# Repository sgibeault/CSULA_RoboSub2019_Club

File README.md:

# CSULA_RoboSub2019_Club
Files for the CSULA RoboSub 2019 club submarine. Her name is M4G1K4RP. 

Sidra's tasks for this week (6/10/19):
- Test barometer in yellow tub in the lab (Tuesday)
- Solder battery connectors and see if we could use the longer tether for next testing (Tuesday)
- Fix library errors with uploading Arduino code over SSH, test this with motherboard on sub (Tuesday)
- Test cameras with CV alg (Wednesday)
- Start working with CV algorithm, set up a plan for training CV -- this means all ROS interfacing between the navigation system and computer vision system should be planned out (Wednesday)
- Install a camera temporarily (Friday)
- Test primitive interface, get a CV system that functions -- doesn't have to detect anything perfectly, just try to get something that works (Friday)

Joseph/Alfonso's tasks for this week (6/10/19):
- Shelving unit laser cut and installed (by Saturday)
- Thruster mounts (by Saturday)

**We will decide on Saturday what the next tasks will be**

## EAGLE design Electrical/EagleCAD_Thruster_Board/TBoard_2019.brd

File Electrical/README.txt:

This folder contains PCB designs, schematics, datasheets, budget forms, and other relevant info and documentation for the electrical systems on the CSULA mini-RoboSub.

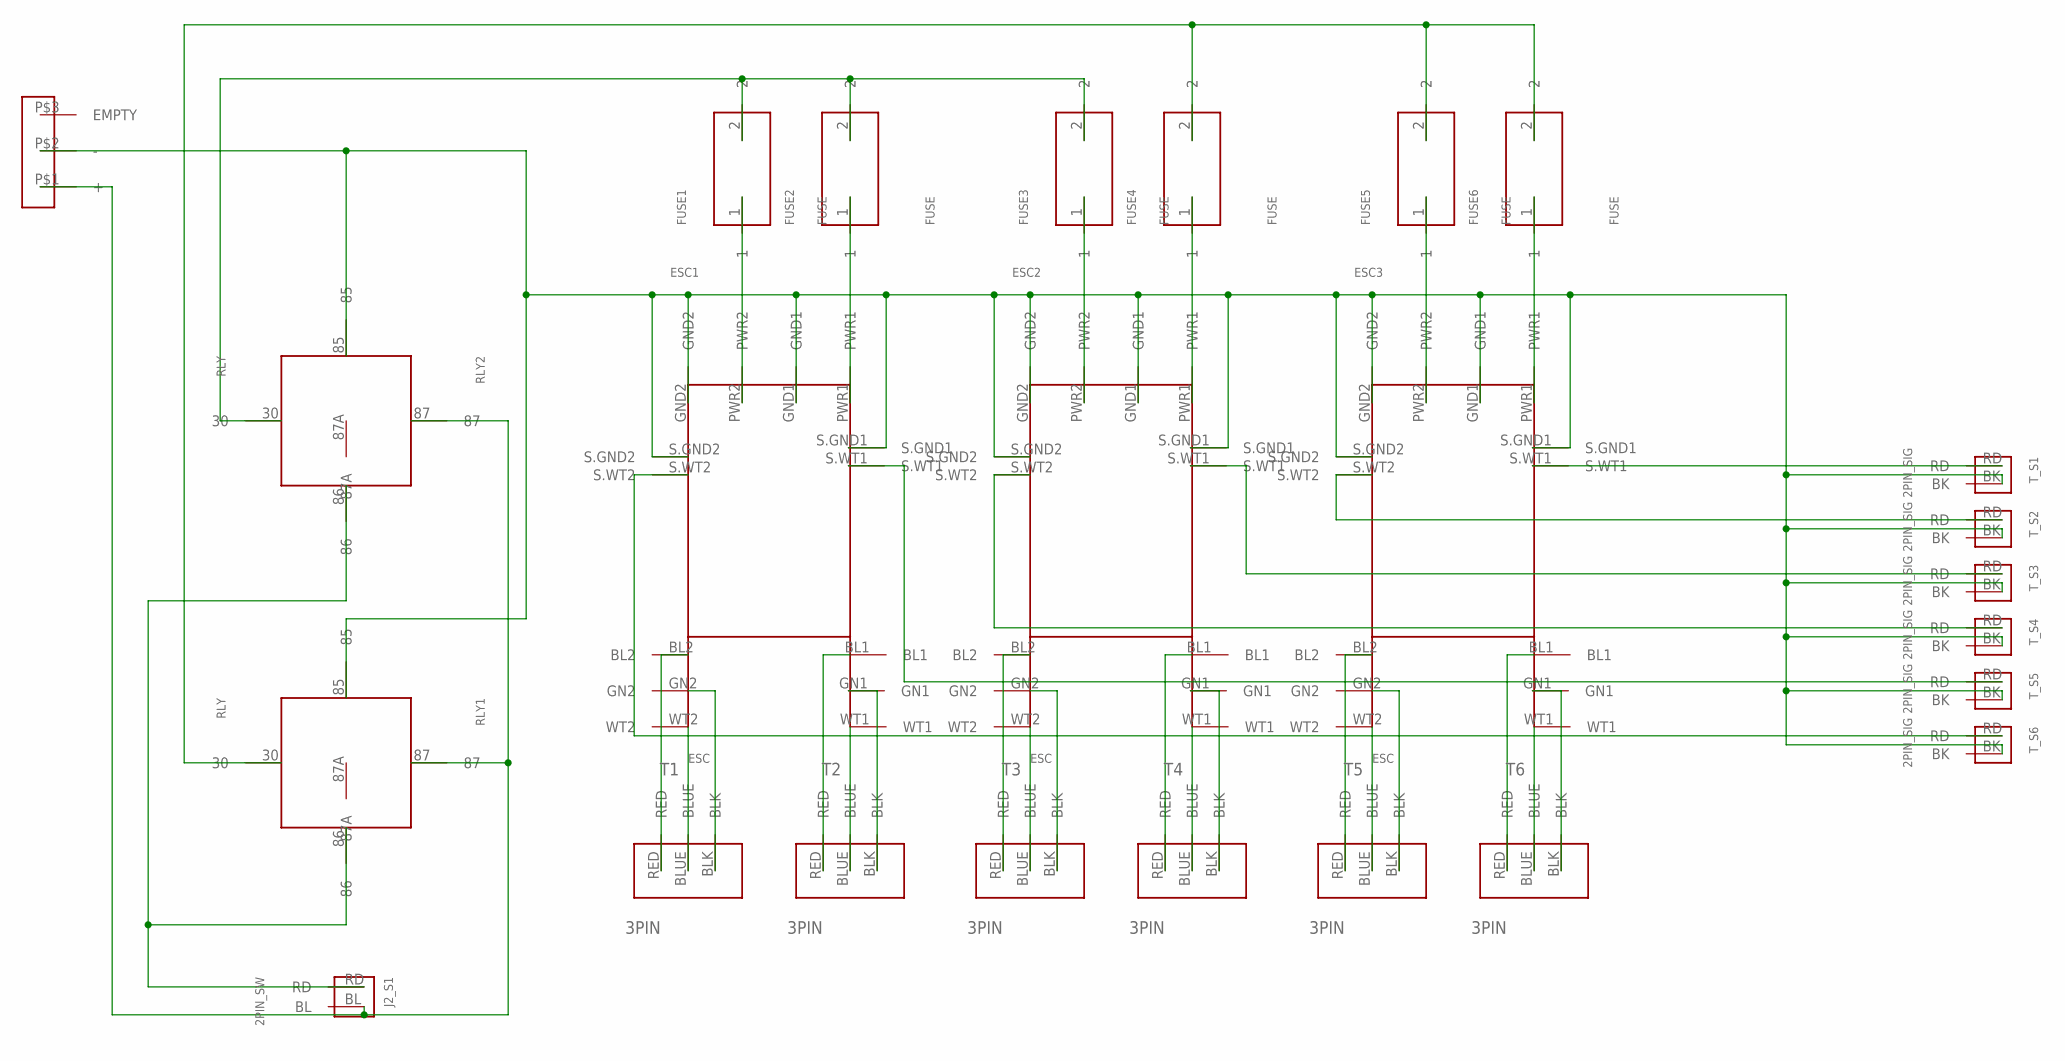
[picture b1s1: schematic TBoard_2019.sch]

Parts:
ESC1, ESC2, ESC3: ESC
FUSE1, FUSE2, FUSE3, FUSE4, FUSE5, FUSE6: FUSE
J2_S1: 2PIN_SW
RLY1, RLY2: RLY
T1, T2, T3, T4, T5, T6: 3PIN
T_S1, T_S2, T_S3, T_S4, T_S5, T_S6: 2PIN_SIG
U$1: TERMINAL

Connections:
unnamed: ESC1.GND1, ESC1.GND2, ESC1.S.GND1, ESC1.S.GND2, ESC2.GND1, ESC2.GND2, ESC2.S.GND1, ESC2.S.GND2, ESC3.GND1, ESC3.GND2, ESC3.S.GND1, ESC3.S.GND2, RLY1.85, RLY2.85, T_S1.BK, T_S2.BK, T_S3.BK, T_S4.BK, T_S5.BK, T_S6.BK, U$1.P$2 (-)
unnamed: J2_S1.BL, RLY1.87, RLY2.87, U$1.P$1 (+)
unnamed: J2_S1.RD, RLY1.86, RLY2.86
unnamed: ESC1.BL2, T1.RED
unnamed: ESC1.GN2, T1.BLK
unnamed: ESC1.WT2, T1.BLUE
unnamed: ESC1.BL1, T2.RED
unnamed: ESC1.GN1, T2.BLK
unnamed: ESC1.WT1, T2.BLUE
unnamed: ESC2.BL2, T3.RED
unnamed: ESC2.GN2, T3.BLK
unnamed: ESC2.WT2, T3.BLUE
unnamed: ESC2.BL1, T4.RED
unnamed: ESC2.GN1, T4.BLK
unnamed: ESC2.WT1, T4.BLUE
unnamed: ESC3.BL2, T5.RED
unnamed: ESC3.GN2, T5.BLK
unnamed: ESC3.WT2, T5.BLUE
unnamed: ESC3.BL1, T6.RED
unnamed: ESC3.GN1, T6.BLK
unnamed: ESC3.WT1, T6.BLUE
unnamed: FUSE4.2, FUSE5.2, FUSE6.2, RLY1.30
unnamed: ESC1.PWR2, FUSE1.1
unnamed: ESC1.PWR1, FUSE2.1
unnamed: ESC2.PWR2, FUSE3.1
unnamed: ESC2.PWR1, FUSE4.1
unnamed: ESC3.PWR2, FUSE5.1
unnamed: ESC3.PWR1, FUSE6.1
unnamed: ESC3.S.WT1, T_S1.RD
unnamed: ESC3.S.WT2, T_S2.RD
unnamed: ESC2.S.WT1, T_S3.RD
unnamed: ESC2.S.WT2, T_S4.RD
unnamed: ESC1.S.WT1, T_S5.RD
unnamed: ESC1.S.WT2, T_S6.RD
unnamed: FUSE1.2, FUSE2.2, FUSE3.2, RLY2.30

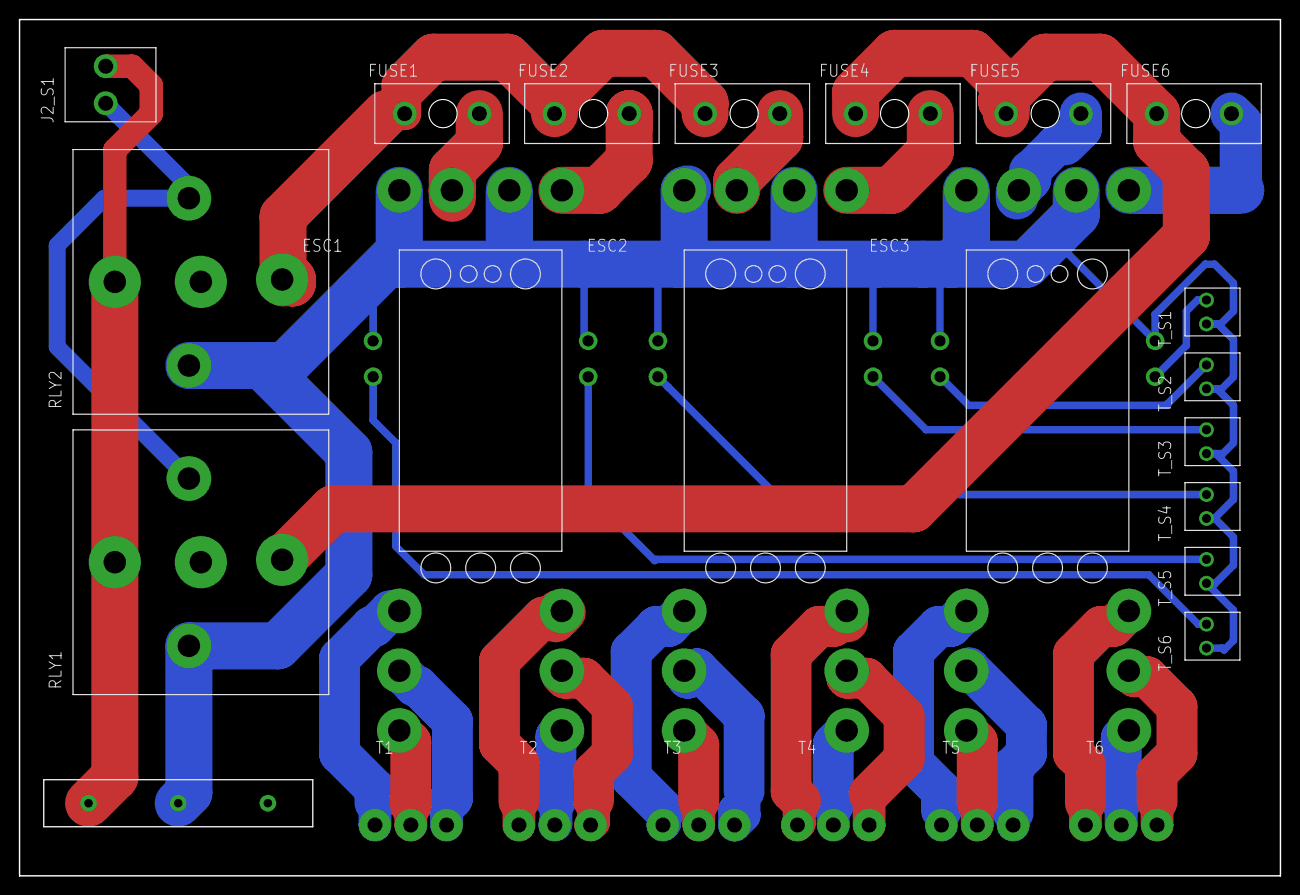
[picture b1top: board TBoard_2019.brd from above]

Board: 2 copper layers, 134.0 x 91.0 mm, 25 parts (0 on the bottom side), 35 nets.

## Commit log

2019-05-31 Create Robosub 2018-2019 Assembly_REV 053019
2019-05-31 Rename Mechanical/Robosub 2018-2019 Assembly_REV 053019 to Robosub 2018-2019 Assembly_REV 053019
2019-05-31 Rename Robosub 2018-2019 Assembly_REV 053019 to Mechanical/Robosub 2018-2019 Assembly_REV 053019
2019-06-09 Rename Stabilization_with_Manual_Control_V1.ino to Stabilization_with_Manual_Control_V1_6.1.19.ino
2019-06-18 Rename Qualification_Attempt.ino to Qualification_Attempt_V1.ino
